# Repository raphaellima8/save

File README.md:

# SAVE – Um sistema FLOSS autônomo para evitar acidentes envolvendo crianças em carros estacionados

## Sobre
SAVE é um sistema autônomo para evitar acidentes envolvendo crianças em carros estacionados.

## Organização dos diretórios
1. src: Código fonte do firmware e esquemáticos do sistema
	* firmware:   Código fonte do firmware
	* schematics: Arquivos de projeto (software Eagle) dos esquemáticos e layout da PCB

2. dist: Arquivos de distribuição
	* firmware: Versão .hex do firmware para gravação na placa Arduino UNO
	* schematics: Versões em PDF do esquemáticos e layouts da PCB para impressão

## Contato
* Raphael Lima: raphael.aolima8 at gmail dot com

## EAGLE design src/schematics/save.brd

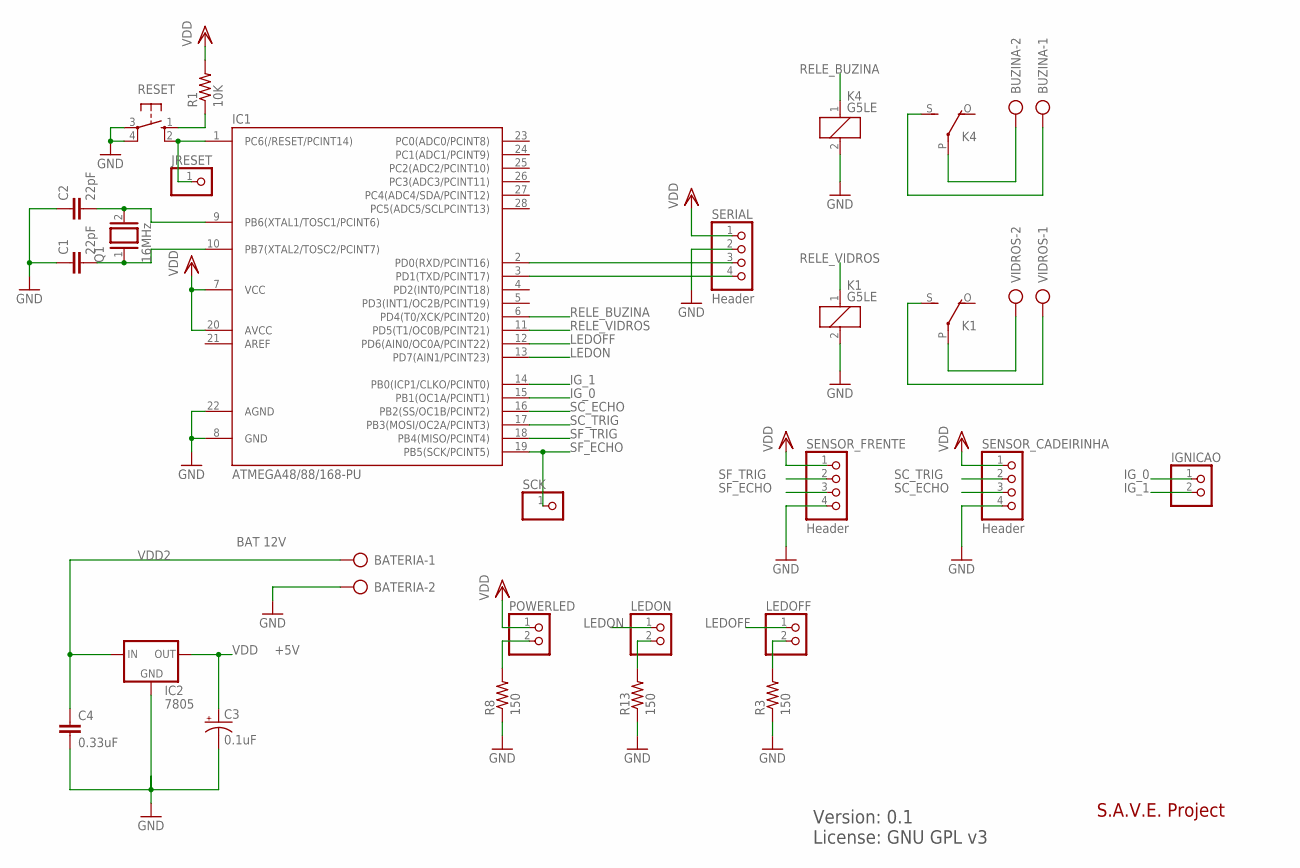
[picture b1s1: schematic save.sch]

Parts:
BATERIA: AK300/2
BUZINA: AK300/2
C1, C2: 22pF; C050-024X044
C3: 0.1uF; E2-4
C4: 0.33uF; C025-030X050
IC1: ATMEGA48/88/168-PU; DIL28-3
IC2: 7805; 78XXL
IGNICAO: PINHD-1X2/90; 1X02/90
JRESET: PINHD-1X1; 1X01
K1, K4: G5LE
LEDOFF: PINHD-1X2/90; 1X02/90
LEDON: PINHD-1X2/90; 1X02/90
POWERLED: PINHD-1X2/90; 1X02/90
Q1: 16MHz; QS
R1: 10K; 0207/10
R3, R8, R13: 150; 0207/10
RESET: 10-XX; B3F-10XX
SCK: PINHD-1X1; 1X01
SENSOR_CADEIRINHA: Header; 1X04
SENSOR_FRENTE: Header; 1X04
SERIAL: Header; 1X04
VIDROS: AK300/2

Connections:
BUZINA-2: BUZINA.2, K4.P
GND: BATERIA.2, C1.1, C2.1, C3.-, C4.2, IC1.8 (GND), IC1.22 (AGND), IC2.GND, K1.2, K4.2, R3.1, R8.1, R13.1, RESET.3, RESET.4 (P1), SENSOR_CADEIRINHA.4, SENSOR_FRENTE.4, SERIAL.2
IG_0: IC1.15 (PB1(OC1A/PCINT1)), IGNICAO.1
IG_1: IC1.14 (PB0(ICP1/CLKO/PCINT0)), IGNICAO.2
LEDOFF: IC1.12 (PD6(AIN0/OC0A/PCINT22)), LEDOFF.1
LEDON: IC1.13 (PD7(AIN1/PCINT23)), LEDON.1
unnamed: BUZINA.1, K4.S
unnamed: R1.1, RESET.1 (S)
unnamed: IC1.1 (PC6(/RESET/PCINT14)), JRESET.1, RESET.2 (S1)
unnamed: C1.2, IC1.10 (PB7(XTAL2/TOSC2/PCINT7)), Q1.1
unnamed: C2.2, IC1.9 (PB6(XTAL1/TOSC1/PCINT6)), Q1.2
unnamed: K1.S, VIDROS.1
unnamed: LEDOFF.2, R3.2
unnamed: K1.P, VIDROS.2
unnamed: POWERLED.2, R8.2
unnamed: LEDON.2, R13.2
RELE_BUZINA: IC1.6 (PD4(T0/XCK/PCINT20)), K4.1
RELE_VIDROS: IC1.11 (PD5(T1/OC0B/PCINT21)), K1.1
RX: IC1.2 (PD0(RXD/PCINT16)), SERIAL.3
SC_ECHO: IC1.16 (PB2(SS/OC1B/PCINT2)), SENSOR_CADEIRINHA.3
SC_TRIG: IC1.17 (PB3(MOSI/OC2A/PCINT3)), SENSOR_CADEIRINHA.2
SF_ECHO: IC1.19 (PB5(SCK/PCINT5)), SCK.1, SENSOR_FRENTE.3
SF_TRIG: IC1.18 (PB4(MISO/PCINT4)), SENSOR_FRENTE.2
TX: IC1.3 (PD1(TXD/PCINT17)), SERIAL.4
VDD: C3.+, IC1.7 (VCC), IC1.20 (AVCC), IC2.OUT, POWERLED.1, R1.2, SENSOR_CADEIRINHA.1, SENSOR_FRENTE.1, SERIAL.1
VDD2: BATERIA.1, C4.1, IC2.IN

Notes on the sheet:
+5V
BAT 12V
S.A.V.E. Project
Version: 0.1 License: GNU GPL v3

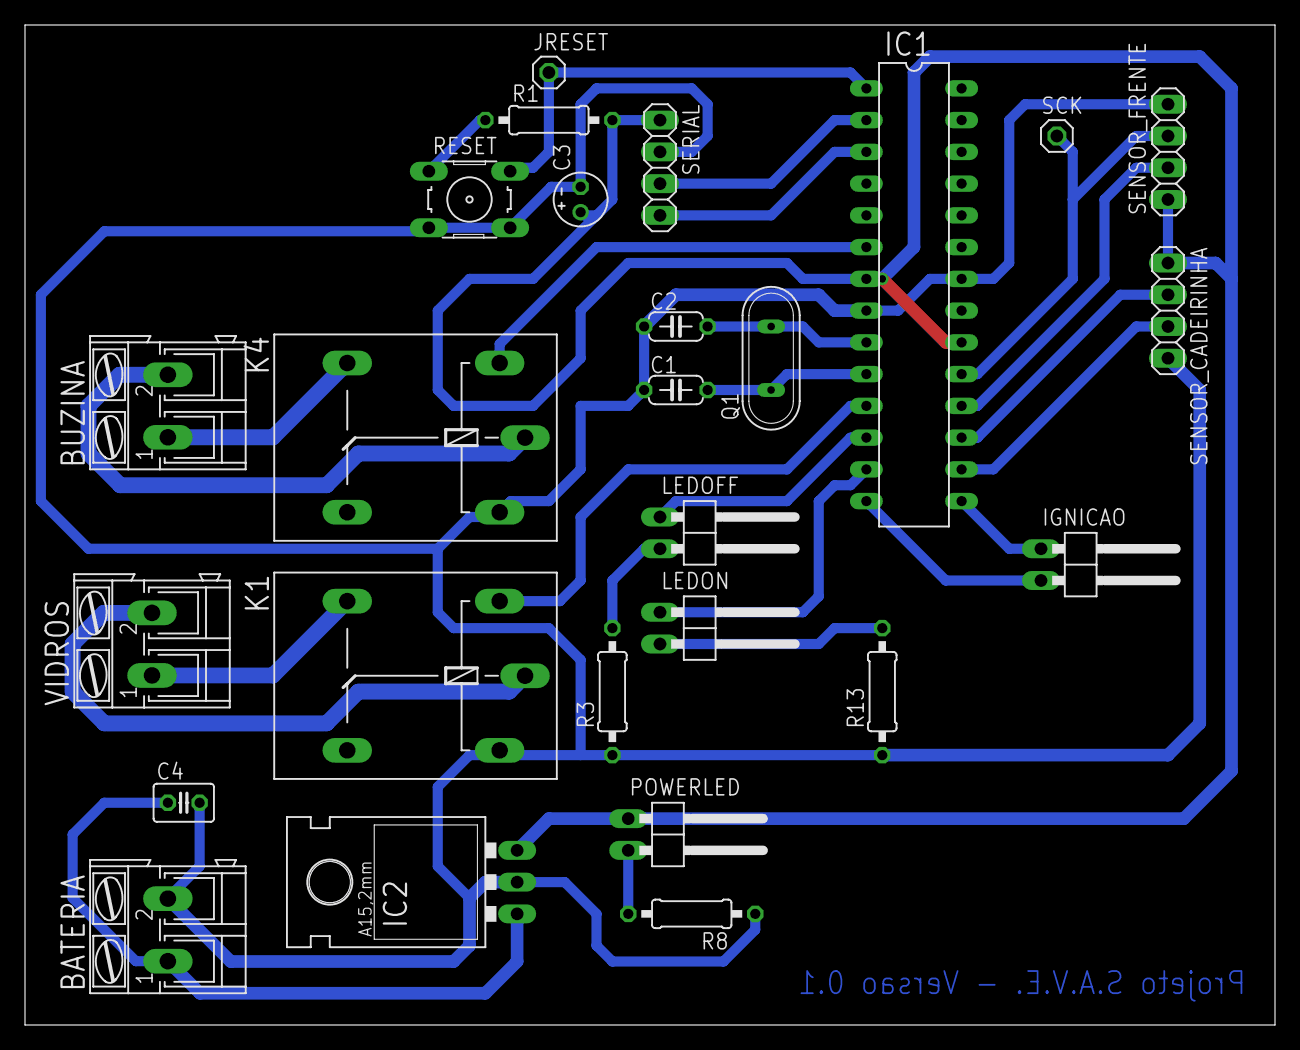
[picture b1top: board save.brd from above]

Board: 2 copper layers, 100.0 x 80.0 mm, 26 parts (0 on the bottom side), 26 nets.

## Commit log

2015-12-24 Innitial commmit
2016-06-24 Schematics and deploy files added.
    - Add schematics sources
    - Add schematics pdf files
    - Add information to README
    - Add hex version of firmware
2016-06-24 Fix README file.
2016-06-24 Fix README
2016-06-25 pt-br for english
2016-06-25 pt-br to english
2016-06-26 Prototype functions added
2016-06-26 weight sensor function added
2016-06-26 Fix conditional of detection
